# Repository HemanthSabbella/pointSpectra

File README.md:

# pointSpectra
pointSpectra is a low-cost, open-source alternative for measuring absorbance of the analyte at specific wavelengths of light. This project is initially made to detect various snake species venom in human blood to do a one-to-one mapping of venom and the snake species using Venom Detection Kit. Nevertheless, it  can be used for any analyte.

> 

**Note:** The whole setup can be built with BOM cost not more than 1000 INR i.e. 15 USD.

# Background

pointSpectra works on the Beer-Lambert law which states that the quantity of light absorbed by a substance dissolved in a fully transmitting solvent is directly proportional to the concentration of the substance and the path length of the light through the solution. The below is the formulation for absorbance of an analyte: 

**Transmittance:**
`T = I / I0`
`% Transmittance: %T = 100 T`

**Absorbance:**
`A = log10 (I0/I)`
`A = log10 (1/T) = -log10 (T)`
`A = log10 (100/%T)`
`A = 2 - log10 (%T)`

# Requirements

**Hardware requirements:**
- [Arduino nano](https://store.arduino.cc/usa/arduino-nano) or [any small form factor arduino](https://store.arduino.cc/usa/arduino/boards-modules)
- [Tx and Rx boards](https://github.com/HemanthSabbella/pointSpectra/tree/main/Tx_Rx_boards%20V1.0)

**Software requirements:**
- [Arduino IDE](https://www.arduino.cc/en/software/)
- [Firmware](https://github.com/HemanthSabbella/pointSpectra/tree/main/firmware)

**Mechanical requirements:**
- [3D-printed case](https://github.com/HemanthSabbella/pointSpectra/tree/main/3D_printed_casing)
- A glass testtube of diameter 5mm.
- Four M3 screws.

# Making 
The setup mainly invoves three boards - Tx Board, Rx Board and Arduino nano. Tx board has wavelength-specific LED emitters that goes through mechanical slits of the 3D printed case in which a glass tube is inserted orthogonally and the unabsorbed light beams coming through the tube, fall on Rx board which has photo diode array that converts the light intensity into proportional frequency. This signal is caputured by the nano-microcontroller, further processing of the data is done and it's followed by plotting the absorbance graph.  

> 
> 

**Tx Board:** 
- Use narrow-band, dominant wavelength LEDs as light sources for a specific wavelength absorbance. 
- 6-point light sources. 
- Adjust the current limiting resistor properly by using forward voltage and current of LEDs, and the supply voltage. 

Spectral Response of 520nm LED: 

> 
> 

**Rx Board:**

- TCS3200 - Light (irradiance) to frequency converter. 
- 8 x 8 array of photodiodes. 
- 16 blue filters, 16 green filters, 16 red filters and 16 clear filters. 
- The output is a square wave (50% duty cycle) with frequency directly proportional to luminous intensity (irradiance).

Functional Block Diagram: 

> 
> 

**3D printed case:**

Use the [cheat sheet](https://github.com/HemanthSabbella/pointSpectra/blob/main/docs/img/3d_print_CS.PNG) of if you are not familiar with 3D printing. We have used fractal works extended printer and print time with infill 50% and layer height 0.2 is 8 hrs. 
> 

**Pin connections:**

| Tx | Arduino nano|
|------|---------|
| LED_520 | D11 |
| LED_560 | D3 |
| LED_600 | D4 |
| LED_630 | D10 |
| LED_660 | D2 |
| GND | GND |
  
| Rx | Arduino nano|
|--------|---------|
| S0 | D5 |
| S1 | D6 |
| S2 | D7 |
| S3 | D8 |
| sensorOut | D9 |

# Firmware
 The firmware code makes the luminous intensity of LEDs same by adjusting the average current to the LEDs using Pulse Width Modulation (PWM) signals. Standard signal conditioning like moving average on the real-time data is preformed to avoid sharp transition due to external environment. Calibration methods - zero referencing and range mapping are used. It outputs an absorbance graph of an analyte by interpolating the sensor reading of 6 narrow band LED inputs. Flash the [Firmware](https://github.com/HemanthSabbella/pointSpectra/tree/main/firmware) using [Arduino IDE](https://www.arduino.cc/en/software/). 
 
# Results 
 We have measured the absorbance of gold nanoparticles with COVID-19 positive and negative samples at 520nm and 630nm (2-points) and repeated it a couple of times, the results are as below: 
>  <br>
>  <br>
> 

# Publication
S C G Kiruba Daniel, Poojitha S Pai, Hemanth Reddy Sabbella, Kumar Singh, Ambica Rangaiah, Shantala Gowdara Basawarajappa, Chetan Singh Thakur, [“Handheld, low-cost, aptamer-based sensing device for rapid SARS-CoV-2 RNA detection using novelly synthesized gold nanoparticles.”](https://ieeexplore.ieee.org/document/9854404) IEEE Sensors Journal, 2022

**Note:** We have been working to test more analytes to validate the robustness of pointSpectra, stay tuned to this space for more results. 

> pointSpectra is developed in [NeuRonICS lab](https://labs.dese.iisc.ac.in/neuronics/), DESE, IISc under the guidance of Dr. Chetan Singh Thakur. For any clarification and details about replication please contact the author at hemanthrs@iisc.ac.in

> Team members: Dr. S. C. G. Kiruba Daniel, Poojitha S Pai

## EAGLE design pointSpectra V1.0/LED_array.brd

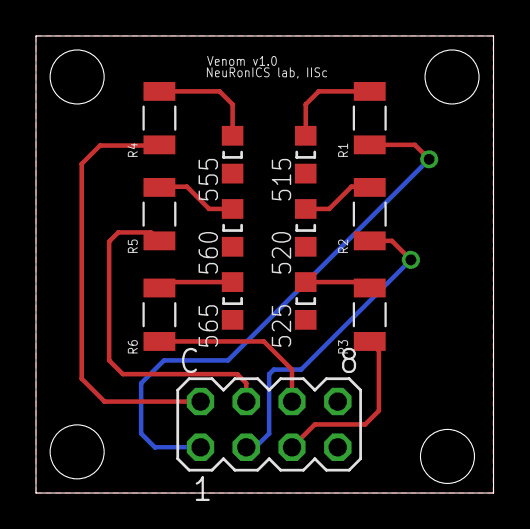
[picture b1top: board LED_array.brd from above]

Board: 2 copper layers, 25.4 x 25.4 mm, 13 parts (0 on the bottom side), 13 nets.

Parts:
515, 520, 525, 555, 560, 565: WUERTH_ELEKTRONIK_150080GS75000WUERTH_ELEKTRONIK_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; WUERTH_ELEKTRONIK_150080GS75000_0
C: MA04-2
R1, R2, R3: 100; RESC3116X65N
R4, R5, R6: 150; RESC3116X65N

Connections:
1: C.1, R1.1
2: C.3, R2.1
3: C.5, R3.1
4: C.2, R4.1
5: C.4, R5.1
6: C.6, R6.1
GND: 515.1, 520.1, 525.1, 555.1, 560.1, 565.1, C.7, C.8
unnamed: 555.2, R4.2
unnamed: 560.2, R5.2
unnamed: 565.2, R6.2
unnamed: 515.2, R1.2
unnamed: 520.2, R2.2
unnamed: 525.2, R3.2

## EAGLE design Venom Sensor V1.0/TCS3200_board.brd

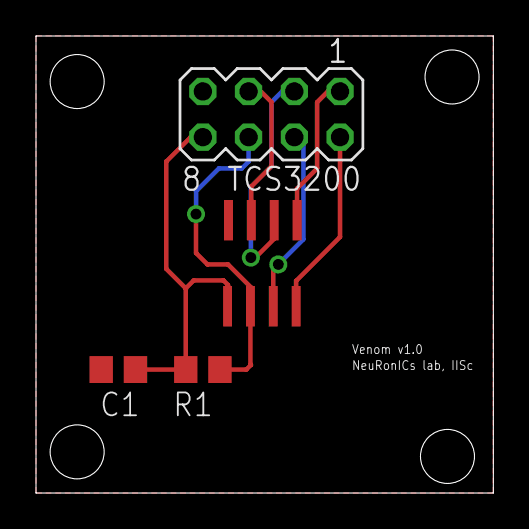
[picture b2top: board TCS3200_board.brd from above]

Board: 2 copper layers, 25.4 x 25.4 mm, 4 parts (0 on the bottom side), 8 nets.

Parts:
C1: 0.1uF; C0805
R1: 10K; R0805
TCS3200: MA04-2
U$1: TCS3200

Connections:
GND: C1.2, TCS3200.7, U$1.4
OUT: R1.1, TCS3200.6, U$1.6
S0: TCS3200.1, U$1.1
S1: TCS3200.3, U$1.2
S2: TCS3200.4, U$1.7
S3: TCS3200.2, U$1.8
VDD: C1.1, R1.2, TCS3200.8, U$1.5
~OE: TCS3200.5, U$1.3

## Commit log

2021-01-13 Updated Venom PCB files, 3D casing files and the presentation
2021-01-13 Spelling mistake correction
2021-05-08 Changes the name of the device
2021-05-08 Added firmware, changes the folder names
2021-06-07 Added pictures
2021-06-07 Added images
2021-06-07 Added more pictures
2021-06-07 Changes the cover image
2021-06-07 increased the picture size
2021-06-07 Added 3d model picture
2021-06-07 Added results
2021-06-07 Added boards
2021-06-07 Anotated the images
2022-07-18 Added Physical Pins Mapping given by Shreyas
